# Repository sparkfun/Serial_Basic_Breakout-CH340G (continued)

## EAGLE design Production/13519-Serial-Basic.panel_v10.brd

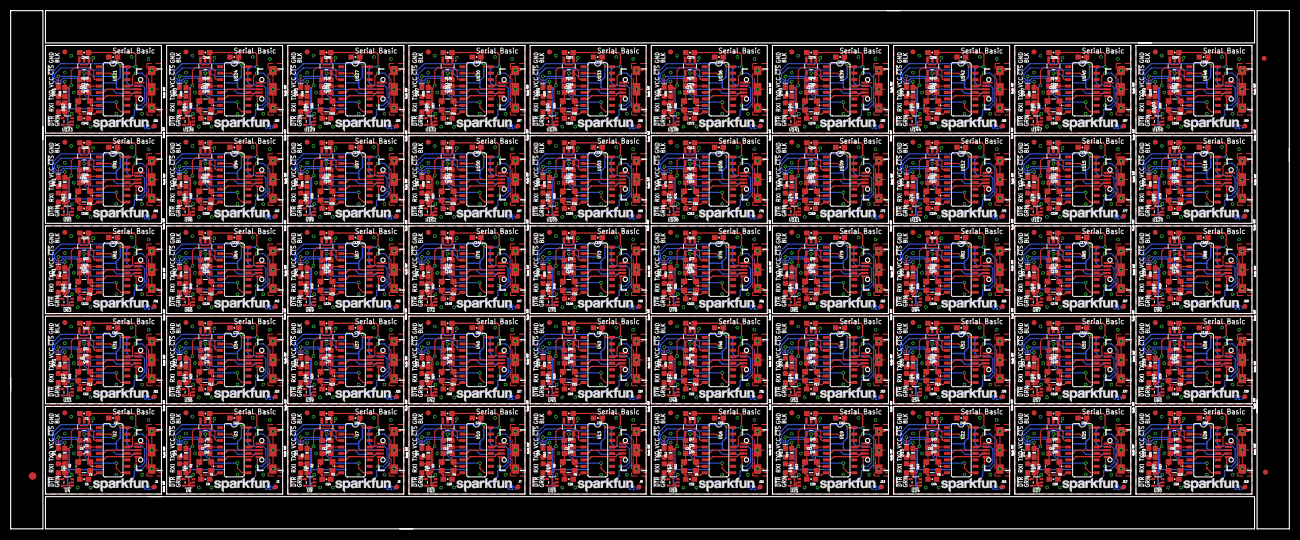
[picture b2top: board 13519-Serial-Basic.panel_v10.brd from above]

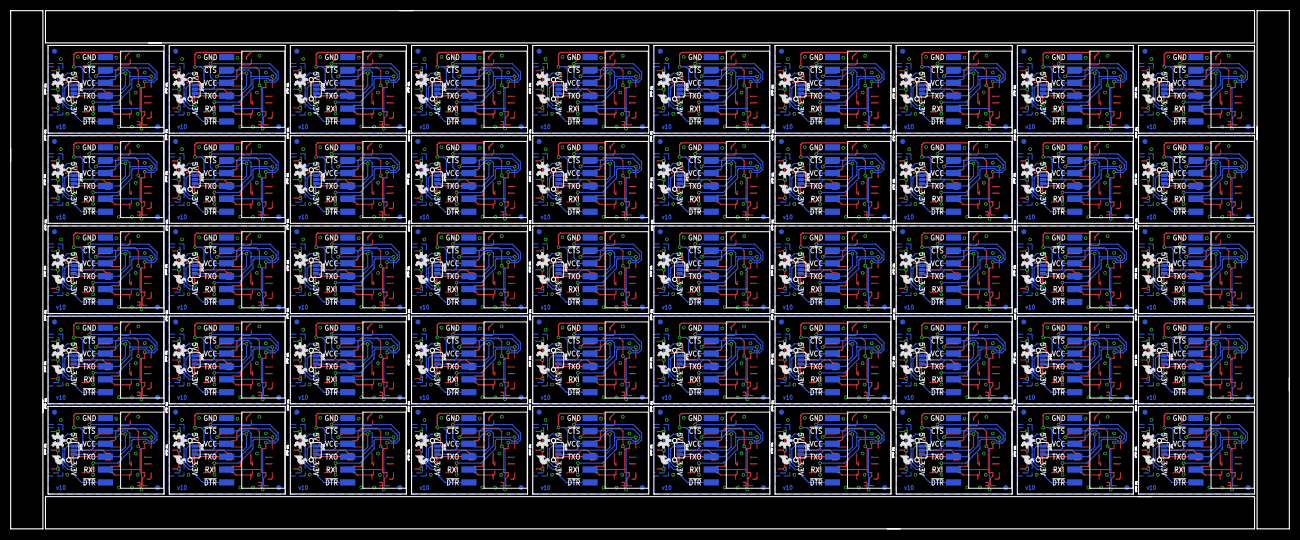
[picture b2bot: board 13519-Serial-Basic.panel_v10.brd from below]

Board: 2 copper layers, 252.0 x 102.1 mm, 1203 parts (300 on the bottom side), 850 nets.

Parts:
C1, C2, C9, C10, C15, C16, C21, C22, C27, C28, C33, C34, C39, C40, C45, C46, C51, C52, C57, C58, C63, C64, C69, C70, C75, C76, C81, C82, C87, C88, C93, C94, C99, C100, C105, C106, C111, C112, C117, C118, C123, C124, C129, C130, C135, C136, C141, C142, C147, C148, C153, C154, C159, C160, C165, C166, C171, C172, C177, C178, C183, C184, C189, C190, C195, C196, C201, C202, C207, C208, C213, C214, C219, C220, C225, C226, C231, C232, C237, C238, C243, C244, C249, C250, C255, C256, C261, C262, C267, C268, C273, C274, C279, C280, C285, C286, C291, C292, C297, C298: 1.0uF; 0603-CAP
C3, C12, C18, C24, C30, C36, C42, C48, C54, C60, C66, C72, C78, C84, C90, C96, C102, C108, C114, C120, C126, C132, C138, C144, C150, C156, C162, C168, C174, C180, C186, C192, C198, C204, C210, C216, C222, C228, C234, C240, C246, C252, C258, C264, C270, C276, C282, C288, C294, C300: 0.1uF; 0603-CAP
C4, C5, C7, C8, C13, C14, C19, C20, C25, C26, C31, C32, C37, C38, C43, C44, C49, C50, C55, C56, C61, C62, C67, C68, C73, C74, C79, C80, C85, C86, C91, C92, C97, C98, C103, C104, C109, C110, C115, C116, C121, C122, C127, C128, C133, C134, C139, C140, C145, C146, C151, C152, C157, C158, C163, C164, C169, C170, C175, C176, C181, C182, C187, C188, C193, C194, C199, C200, C205, C206, C211, C212, C217, C218, C223, C224, C229, C230, C235, C236, C241, C242, C247, C248, C253, C254, C259, C260, C265, C266, C271, C272, C277, C278, C283, C284, C289, C290, C295, C296: 10pF; 0603-CAP
C6, C11, C17, C23, C29, C35, C41, C47, C53, C59, C65, C71, C77, C83, C89, C95, C101, C107, C113, C119, C125, C131, C137, C143, C149, C155, C161, C167, C173, C179, C185, C191, C197, C203, C209, C215, C221, C227, C233, C239, C245, C251, C257, C263, C269, C275, C281, C287, C293, C299: 10nF; 0603-CAP
D1, D3, D5, D7, D9, D11, D13, D15, D17, D19, D21, D23, D25, D27, D29, D31, D33, D35, D37, D39, D41, D43, D45, D47, D49, D51, D53, D55, D57, D59, D61, D63, D65, D67, D69, D71, D73, D75, D77, D79, D81, D83, D85, D87, D89, D91, D93, D95, D97, D99: GREEN; LED-0603
D2, D4, D6, D8, D10, D12, D14, D16, D18, D20, D22, D24, D26, D28, D30, D32, D34, D36, D38, D40, D42, D44, D46, D48, D50, D52, D54, D56, D58, D60, D62, D64, D66, D68, D70, D72, D74, D76, D78, D80, D82, D84, D86, D88, D90, D92, D94, D96, D98, D100: Yellow; LED-0603
E$1: FIDUCIAL-1.5X3
E$5, E$6: FIDUCIAL-1X2
J1, J3, J5, J7, J9, J11, J13, J15, J17, J19, J21, J23, J25, J27, J29, J31, J33, J35, J37, J39, J41, J43, J45, J47, J49, J51, J53, J55, J57, J59, J61, J63, J65, J67, J69, J71, J73, J75, J77, J79, J81, J83, J85, J87, J89, J91, J93, J95, J97, J99: microB; USB-B-MICRO-SMD_V03
J2, J4, J6, J8, J10, J12, J14, J16, J18, J20, J22, J24, J26, J28, J30, J32, J34, J36, J38, J40, J42, J44, J46, J48, J50, J52, J54, J56, J58, J60, J62, J64, J66, J68, J70, J72, J74, J76, J78, J80, J82, J84, J86, J88, J90, J92, J94, J96, J98, J100: 1X06-SMD-FEMALE-V2
JP1, JP10, JP15, JP20, JP25, JP30, JP35, JP40, JP45, JP50, JP55, JP60, JP65, JP70, JP75, JP80, JP85, JP90, JP95, JP100, JP105, JP110, JP115, JP120, JP125, JP130, JP135, JP140, JP145, JP150, JP155, JP160, JP165, JP170, JP175, JP180, JP185, JP190, JP195, JP200, JP205, JP210, JP215, JP220, JP225, JP230, JP235, JP240, JP245, JP250: PAD-JUMPER-3-2OF3_NC_BY_PASTE_YES_SILK_FULL_BOX
JP2, JP3, JP4, JP5, JP6, JP7, JP8, JP9, JP11, JP12, JP13, JP14, JP16, JP17, JP18, JP19, JP21, JP22, JP23, JP24, JP26, JP27, JP28, JP29, JP31, JP32, JP33, JP34, JP36, JP37, JP38, JP39, JP41, JP42, JP43, JP44, JP46, JP47, JP48, JP49, JP51, JP52, JP53, JP54, JP56, JP57, JP58, JP59, JP61, JP62, JP63, JP64, JP66, JP67, JP68, JP69, JP71, JP72, JP73, JP74, JP76, JP77, JP78, JP79, JP81, JP82, JP83, JP84, JP86, JP87, JP88, JP89, JP91, JP92, JP93, JP94, JP96, JP97, JP98, JP99, JP101, JP102, JP103, JP104, JP106, JP107, JP108, JP109, JP111, JP112, JP113, JP114, JP116, JP117, JP118, JP119, JP121, JP122, JP123, JP124, JP126, JP127, JP128, JP129, JP131, JP132, JP133, JP134, JP136, JP137, JP138, JP139, JP141, JP142, JP143, JP144, JP146, JP147, JP148, JP149, JP151, JP152, JP153, JP154, JP156, JP157, JP158, JP159, JP161, JP162, JP163, JP164, JP166, JP167, JP168, JP169, JP171, JP172, JP173, JP174, JP176, JP177, JP178, JP179, JP181, JP182, JP183, JP184, JP186, JP187, JP188, JP189, JP191, JP192, JP193, JP194, JP196, JP197, JP198, JP199, JP201, JP202, JP203, JP204, JP206, JP207, JP208, JP209, JP211, JP212, JP213, JP214, JP216, JP217, JP218, JP219, JP221, JP222, JP223, JP224, JP226, JP227, JP228, JP229, JP231, JP232, JP233, JP234, JP236, JP237, JP238, JP239, JP241, JP242, JP243, JP244, JP246, JP247, JP248, JP249: FIDUCIAL1X2; FIDUCIAL-1X2
LOGO1, LOGO4, LOGO7, LOGO10, LOGO13, LOGO16, LOGO19, LOGO22, LOGO25, LOGO28, LOGO31, LOGO34, LOGO37, LOGO40, LOGO43, LOGO46, LOGO49, LOGO52, LOGO55, LOGO58, LOGO61, LOGO64, LOGO67, LOGO70, LOGO73, LOGO76, LOGO79, LOGO82, LOGO85, LOGO88, LOGO91, LOGO94, LOGO97, LOGO100, LOGO103, LOGO106, LOGO109, LOGO112, LOGO115, LOGO118, LOGO121, LOGO124, LOGO127, LOGO130, LOGO133, LOGO136, LOGO139, LOGO142, LOGO145, LOGO148: OSHW-LOGOS; OSHW-LOGO-S
LOGO2, LOGO6, LOGO9, LOGO12, LOGO15, LOGO18, LOGO21, LOGO24, LOGO27, LOGO30, LOGO33, LOGO36, LOGO39, LOGO42, LOGO45, LOGO48, LOGO51, LOGO54, LOGO57, LOGO60, LOGO63, LOGO66, LOGO69, LOGO72, LOGO75, LOGO78, LOGO81, LOGO84, LOGO87, LOGO90, LOGO93, LOGO96, LOGO99, LOGO102, LOGO105, LOGO108, LOGO111, LOGO114, LOGO117, LOGO120, LOGO123, LOGO126, LOGO129, LOGO132, LOGO135, LOGO138, LOGO141, LOGO144, LOGO147, LOGO150: SFE_LOGO_FLAME.1_INCH; SFE_LOGO_FLAME_.1
LOGO3, LOGO5, LOGO8, LOGO11, LOGO14, LOGO17, LOGO20, LOGO23, LOGO26, LOGO29, LOGO32, LOGO35, LOGO38, LOGO41, LOGO44, LOGO47, LOGO50, LOGO53, LOGO56, LOGO59, LOGO62, LOGO65, LOGO68, LOGO71, LOGO74, LOGO77, LOGO80, LOGO83, LOGO86, LOGO89, LOGO92, LOGO95, LOGO98, LOGO101, LOGO104, LOGO107, LOGO110, LOGO113, LOGO116, LOGO119, LOGO122, LOGO125, LOGO128, LOGO131, LOGO134, LOGO137, LOGO140, LOGO143, LOGO146, LOGO149: SFE_LOGO_NAME.1_INCH; SFE_LOGO_NAME_.1
R1, R2, R5, R7, R9, R11, R13, R15, R17, R19, R21, R23, R25, R27, R29, R31, R33, R35, R37, R39, R41, R43, R45, R47, R49, R51, R53, R55, R57, R59, R61, R63, R65, R67, R69, R71, R73, R75, R77, R79, R81, R83, R85, R87, R89, R91, R93, R95, R97, R99: 1K; 0603-RES
R3, R4, R6, R8, R10, R12, R14, R16, R18, R20, R22, R24, R26, R28, R30, R32, R34, R36, R38, R40, R42, R44, R46, R48, R50, R52, R54, R56, R58, R60, R62, R64, R66, R68, R70, R72, R74, R76, R78, R80, R82, R84, R86, R88, R90, R92, R94, R96, R98, R100: 330; 0603-RES
U1, U5, U8, U11, U14, U17, U20, U23, U26, U29, U32, U35, U38, U41, U44, U47, U50, U53, U56, U59, U62, U65, U68, U71, U74, U77, U80, U83, U86, U89, U92, U95, U98, U101, U104, U107, U110, U113, U116, U119, U122, U125, U128, U131, U134, U137, U140, U143, U146, U149: AP2112-3.3V; SOT23-5
U2, U3, U7, U10, U13, U16, U19, U22, U25, U28, U31, U34, U37, U40, U43, U46, U49, U52, U55, U58, U61, U64, U67, U70, U73, U76, U79, U82, U85, U88, U91, U94, U97, U100, U103, U106, U109, U112, U115, U118, U121, U124, U127, U130, U133, U136, U139, U142, U145, U148: CH340G; SO016
U4, U6, U9, U12, U15, U18, U21, U24, U27, U30, U33, U36, U39, U42, U45, U48, U51, U54, U57, U60, U63, U66, U69, U72, U75, U78, U81, U84, U87, U90, U93, U96, U99, U102, U105, U108, U111, U114, U117, U120, U123, U126, U129, U132, U135, U138, U141, U144, U147, U150: 74LVC1G08SE; SOT353
Y1, Y2, Y3, Y4, Y5, Y6, Y7, Y8, Y9, Y10, Y11, Y12, Y13, Y14, Y15, Y16, Y17, Y18, Y19, Y20, Y21, Y22, Y23, Y24, Y25, Y26, Y27, Y28, Y29, Y30, Y31, Y32, Y33, Y34, Y35, Y36, Y37, Y38, Y39, Y40, Y41, Y42, Y43, Y44, Y45, Y46, Y47, Y48, Y49, Y50: 12MHz; CRYSTAL-SMD-3.2X2.5

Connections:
3.3V: C2.1, JP1.3, U1.5
3.3V1: C10.1, JP10.3, U5.5
3.3V2: C16.1, JP15.3, U8.5
3.3V3: C22.1, JP20.3, U11.5
3.3V4: C28.1, JP25.3, U14.5
3.3V5: C34.1, JP30.3, U17.5
3.3V6: C40.1, JP35.3, U20.5
3.3V7: C46.1, JP40.3, U23.5
3.3V8: C52.1, JP45.3, U26.5
3.3V9: C58.1, JP50.3, U29.5
3.3V10: C64.1, JP55.3, U32.5
3.3V11: C70.1, JP60.3, U35.5
3.3V12: C76.1, JP65.3, U38.5
3.3V13: C82.1, JP70.3, U41.5
3.3V14: C88.1, JP75.3, U44.5
3.3V15: C94.1, JP80.3, U47.5
3.3V16: C100.1, JP85.3, U50.5
3.3V17: C106.1, JP90.3, U53.5
3.3V18: C112.1, JP95.3, U56.5
3.3V19: C118.1, JP100.3, U59.5
3.3V20: C124.1, JP105.3, U62.5
3.3V21: C130.1, JP110.3, U65.5
3.3V22: C136.1, JP115.3, U68.5
3.3V23: C142.1, JP120.3, U71.5
3.3V24: C148.1, JP125.3, U74.5
3.3V25: C154.1, JP130.3, U77.5
3.3V26: C160.1, JP135.3, U80.5
3.3V27: C166.1, JP140.3, U83.5
3.3V28: C172.1, JP145.3, U86.5
3.3V29: C178.1, JP150.3, U89.5
3.3V30: C184.1, JP155.3, U92.5
3.3V31: C190.1, JP160.3, U95.5
3.3V32: C196.1, JP165.3, U98.5
3.3V33: C202.1, JP170.3, U101.5
3.3V34: C208.1, JP175.3, U104.5
3.3V35: C214.1, JP180.3, U107.5
3.3V36: C220.1, JP185.3, U110.5
3.3V37: C226.1, JP190.3, U113.5
3.3V38: C232.1, JP195.3, U116.5
3.3V39: C238.1, JP200.3, U119.5
3.3V40: C244.1, JP205.3, U122.5
3.3V41: C250.1, JP210.3, U125.5
3.3V42: C256.1, JP215.3, U128.5
3.3V43: C262.1, JP220.3, U131.5
3.3V44: C268.1, JP225.3, U134.5
3.3V45: C274.1, JP230.3, U137.5
3.3V46: C280.1, JP235.3, U140.5
3.3V47: C286.1, JP240.3, U143.5
3.3V48: C292.1, JP245.3, U146.5
3.3V49: C298.1, JP250.3, U149.5
5V: C1.1, J1.VBUS, JP1.1, U1.1, U1.3
5V1: C9.1, J3.VBUS, JP10.1, U5.1, U5.3
5V2: C15.1, J5.VBUS, JP15.1, U8.1, U8.3
5V3: C21.1, J7.VBUS, JP20.1, U11.1, U11.3
5V4: C27.1, J9.VBUS, JP25.1, U14.1, U14.3
5V5: C33.1, J11.VBUS, JP30.1, U17.1, U17.3
5V6: C39.1, J13.VBUS, JP35.1, U20.1, U20.3
5V7: C45.1, J15.VBUS, JP40.1, U23.1, U23.3
5V8: C51.1, J17.VBUS, JP45.1, U26.1, U26.3
5V9: C57.1, J19.VBUS, JP50.1, U29.1, U29.3
5V10: C63.1, J21.VBUS, JP55.1, U32.1, U32.3
5V11: C69.1, J23.VBUS, JP60.1, U35.1, U35.3
5V12: C75.1, J25.VBUS, JP65.1, U38.1, U38.3
5V13: C81.1, J27.VBUS, JP70.1, U41.1, U41.3
5V14: C87.1, J29.VBUS, JP75.1, U44.1, U44.3
5V15: C93.1, J31.VBUS, JP80.1, U47.1, U47.3
5V16: C99.1, J33.VBUS, JP85.1, U50.1, U50.3
5V17: C105.1, J35.VBUS, JP90.1, U53.1, U53.3
5V18: C111.1, J37.VBUS, JP95.1, U56.1, U56.3
5V19: C117.1, J39.VBUS, JP100.1, U59.1, U59.3
5V20: C123.1, J41.VBUS, JP105.1, U62.1, U62.3
5V21: C129.1, J43.VBUS, JP110.1, U65.1, U65.3
5V22: C135.1, J45.VBUS, JP115.1, U68.1, U68.3
5V23: C141.1, J47.VBUS, JP120.1, U71.1, U71.3
5V24: C147.1, J49.VBUS, JP125.1, U74.1, U74.3
5V25: C153.1, J51.VBUS, JP130.1, U77.1, U77.3
5V26: C159.1, J53.VBUS, JP135.1, U80.1, U80.3
5V27: C165.1, J55.VBUS, JP140.1, U83.1, U83.3
5V28: C171.1, J57.VBUS, JP145.1, U86.1, U86.3
5V29: C177.1, J59.VBUS, JP150.1, U89.1, U89.3
5V30: C183.1, J61.VBUS, JP155.1, U92.1, U92.3
5V31: C189.1, J63.VBUS, JP160.1, U95.1, U95.3
5V32: C195.1, J65.VBUS, JP165.1, U98.1, U98.3
5V33: C201.1, J67.VBUS, JP170.1, U101.1, U101.3
5V34: C207.1, J69.VBUS, JP175.1, U104.1, U104.3
5V35: C213.1, J71.VBUS, JP180.1, U107.1, U107.3
5V36: C219.1, J73.VBUS, JP185.1, U110.1, U110.3
5V37: C225.1, J75.VBUS, JP190.1, U113.1, U113.3
5V38: C231.1, J77.VBUS, JP195.1, U116.1, U116.3
5V39: C237.1, J79.VBUS, JP200.1, U119.1, U119.3
5V40: C243.1, J81.VBUS, JP205.1, U122.1, U122.3
5V41: C249.1, J83.VBUS, JP210.1, U125.1, U125.3
5V42: C255.1, J85.VBUS, JP215.1, U128.1, U128.3
5V43: C261.1, J87.VBUS, JP220.1, U131.1, U131.3
5V44: C267.1, J89.VBUS, JP225.1, U134.1, U134.3
5V45: C273.1, J91.VBUS, JP230.1, U137.1, U137.3
5V46: C279.1, J93.VBUS, JP235.1, U140.1, U140.3
5V47: C285.1, J95.VBUS, JP240.1, U143.1, U143.3
5V48: C291.1, J97.VBUS, JP245.1, U146.1, U146.3
5V49: C297.1, J99.VBUS, JP250.1, U149.1, U149.3
!CTS: J2.2, U2.9
!CTS1: J4.2, U3.9
!CTS2: J6.2, U7.9
!CTS3: J8.2, U10.9
!CTS4: J10.2, U13.9
!CTS5: J12.2, U16.9
!CTS6: J14.2, U19.9
!CTS7: J16.2, U22.9
!CTS8: J18.2, U25.9
!CTS9: J20.2, U28.9
!CTS10: J22.2, U31.9
!CTS11: J24.2, U34.9
!CTS12: J26.2, U37.9
!CTS13: J28.2, U40.9
!CTS14: J30.2, U43.9
!CTS15: J32.2, U46.9
!CTS16: J34.2, U49.9
!CTS17: J36.2, U52.9
!CTS18: J38.2, U55.9
!CTS19: J40.2, U58.9
!CTS20: J42.2, U61.9
!CTS21: J44.2, U64.9
!CTS22: J46.2, U67.9
!CTS23: J48.2, U70.9
!CTS24: J50.2, U73.9
!CTS25: J52.2, U76.9
!CTS26: J54.2, U79.9
!CTS27: J56.2, U82.9
!CTS28: J58.2, U85.9
!CTS29: J60.2, U88.9
!CTS30: J62.2, U91.9
!CTS31: J64.2, U94.9
!CTS32: J66.2, U97.9
!CTS33: J68.2, U100.9
!CTS34: J70.2, U103.9
!CTS35: J72.2, U106.9
!CTS36: J74.2, U109.9
!CTS37: J76.2, U112.9
!CTS38: J78.2, U115.9
!CTS39: J80.2, U118.9
!CTS40: J82.2, U121.9
!CTS41: J84.2, U124.9
!CTS42: J86.2, U127.9
!CTS43: J88.2, U130.9
!CTS44: J90.2, U133.9
!CTS45: J92.2, U136.9
!CTS46: J94.2, U139.9
!CTS47: J96.2, U142.9
!CTS48: J98.2, U145.9
!CTS49: J100.2, U148.9
!DTR: J2.6, U2.13
!DTR1: J4.6, U3.13
!DTR2: J6.6, U7.13
!DTR3: J8.6, U10.13
!DTR4: J10.6, U13.13
!DTR5: J12.6, U16.13
!DTR6: J14.6, U19.13
!DTR7: J16.6, U22.13
!DTR8: J18.6, U25.13
!DTR9: J20.6, U28.13
!DTR10: J22.6, U31.13
!DTR11: J24.6, U34.13
!DTR12: J26.6, U37.13
!DTR13: J28.6, U40.13
!DTR14: J30.6, U43.13
!DTR15: J32.6, U46.13
!DTR16: J34.6, U49.13
!DTR17: J36.6, U52.13
!DTR18: J38.6, U55.13
!DTR19: J40.6, U58.13
!DTR20: J42.6, U61.13
!DTR21: J44.6, U64.13
!DTR22: J46.6, U67.13
!DTR23: J48.6, U70.13
!DTR24: J50.6, U73.13
!DTR25: J52.6, U76.13
!DTR26: J54.6, U79.13
!DTR27: J56.6, U82.13
!DTR28: J58.6, U85.13
!DTR29: J60.6, U88.13
!DTR30: J62.6, U91.13
!DTR31: J64.6, U94.13
!DTR32: J66.6, U97.13
!DTR33: J68.6, U100.13
!DTR34: J70.6, U103.13
!DTR35: J72.6, U106.13
!DTR36: J74.6, U109.13
!DTR37: J76.6, U112.13
!DTR38: J78.6, U115.13
!DTR39: J80.6, U118.13
!DTR40: J82.6, U121.13
!DTR41: J84.6, U124.13
!DTR42: J86.6, U127.13
!DTR43: J88.6, U130.13
!DTR44: J90.6, U133.13
!DTR45: J92.6, U136.13
!DTR46: J94.6, U139.13
!DTR47: J96.6, U142.13
!DTR48: J98.6, U145.13
!DTR49: J100.6, U148.13
GND: C1.2, C2.2, C3.2, C4.1, C5.1, C6.2, J1.GND, J2.1, U1.2, U2.1, U4.3, Y2.2, Y2.4
GND1: C7.1, C8.1, C9.2, C10.2, C11.2, C12.2, J3.GND, J4.1, U3.1, U5.2, U6.3, Y1.2, Y1.4
GND2: C13.1, C14.1, C15.2, C16.2, C17.2, C18.2, J5.GND, J6.1, U7.1, U8.2, U9.3, Y3.2, Y3.4
GND3: C19.1, C20.1, C21.2, C22.2, C23.2, C24.2, J7.GND, J8.1, U10.1, U11.2, U12.3, Y4.2, Y4.4
GND4: C25.1, C26.1, C27.2, C28.2, C29.2, C30.2, J9.GND, J10.1, U13.1, U14.2, U15.3, Y5.2, Y5.4
GND5: C31.1, C32.1, C33.2, C34.2, C35.2, C36.2, J11.GND, J12.1, U16.1, U17.2, U18.3, Y6.2, Y6.4
GND6: C37.1, C38.1, C39.2, C40.2, C41.2, C42.2, J13.GND, J14.1, U19.1, U20.2, U21.3, Y7.2, Y7.4
GND7: C43.1, C44.1, C45.2, C46.2, C47.2, C48.2, J15.GND, J16.1, U22.1, U23.2, U24.3, Y8.2, Y8.4
GND8: C49.1, C50.1, C51.2, C52.2, C53.2, C54.2, J17.GND, J18.1, U25.1, U26.2, U27.3, Y9.2, Y9.4
GND9: C55.1, C56.1, C57.2, C58.2, C59.2, C60.2, J19.GND, J20.1, U28.1, U29.2, U30.3, Y10.2, Y10.4
GND10: C61.1, C62.1, C63.2, C64.2, C65.2, C66.2, J21.GND, J22.1, U31.1, U32.2, U33.3, Y11.2, Y11.4
GND11: C67.1, C68.1, C69.2, C70.2, C71.2, C72.2, J23.GND, J24.1, U34.1, U35.2, U36.3, Y12.2, Y12.4
GND12: C73.1, C74.1, C75.2, C76.2, C77.2, C78.2, J25.GND, J26.1, U37.1, U38.2, U39.3, Y13.2, Y13.4
GND13: C79.1, C80.1, C81.2, C82.2, C83.2, C84.2, J27.GND, J28.1, U40.1, U41.2, U42.3, Y14.2, Y14.4
GND14: C85.1, C86.1, C87.2, C88.2, C89.2, C90.2, J29.GND, J30.1, U43.1, U44.2, U45.3, Y15.2, Y15.4
GND15: C91.1, C92.1, C93.2, C94.2, C95.2, C96.2, J31.GND, J32.1, U46.1, U47.2, U48.3, Y16.2, Y16.4
GND16: C97.1, C98.1, C99.2, C100.2, C101.2, C102.2, J33.GND, J34.1, U49.1, U50.2, U51.3, Y17.2, Y17.4
GND17: C103.1, C104.1, C105.2, C106.2, C107.2, C108.2, J35.GND, J36.1, U52.1, U53.2, U54.3, Y18.2, Y18.4
GND18: C109.1, C110.1, C111.2, C112.2, C113.2, C114.2, J37.GND, J38.1, U55.1, U56.2, U57.3, Y19.2, Y19.4
GND19: C115.1, C116.1, C117.2, C118.2, C119.2, C120.2, J39.GND, J40.1, U58.1, U59.2, U60.3, Y20.2, Y20.4
GND20: C121.1, C122.1, C123.2, C124.2, C125.2, C126.2, J41.GND, J42.1, U61.1, U62.2, U63.3, Y21.2, Y21.4
GND21: C127.1, C128.1, C129.2, C130.2, C131.2, C132.2, J43.GND, J44.1, U64.1, U65.2, U66.3, Y22.2, Y22.4
GND22: C133.1, C134.1, C135.2, C136.2, C137.2, C138.2, J45.GND, J46.1, U67.1, U68.2, U69.3, Y23.2, Y23.4
GND23: C139.1, C140.1, C141.2, C142.2, C143.2, C144.2, J47.GND, J48.1, U70.1, U71.2, U72.3, Y24.2, Y24.4
GND24: C145.1, C146.1, C147.2, C148.2, C149.2, C150.2, J49.GND, J50.1, U73.1, U74.2, U75.3, Y25.2, Y25.4
GND25: C151.1, C152.1, C153.2, C154.2, C155.2, C156.2, J51.GND, J52.1, U76.1, U77.2, U78.3, Y26.2, Y26.4
GND26: C157.1, C158.1, C159.2, C160.2, C161.2, C162.2, J53.GND, J54.1, U79.1, U80.2, U81.3, Y27.2, Y27.4
GND27: C163.1, C164.1, C165.2, C166.2, C167.2, C168.2, J55.GND, J56.1, U82.1, U83.2, U84.3, Y28.2, Y28.4
GND28: C169.1, C170.1, C171.2, C172.2, C173.2, C174.2, J57.GND, J58.1, U85.1, U86.2, U87.3, Y29.2, Y29.4
GND29: C175.1, C176.1, C177.2, C178.2, C179.2, C180.2, J59.GND, J60.1, U88.1, U89.2, U90.3, Y30.2, Y30.4
GND30: C181.1, C182.1, C183.2, C184.2, C185.2, C186.2, J61.GND, J62.1, U91.1, U92.2, U93.3, Y31.2, Y31.4
GND31: C187.1, C188.1, C189.2, C190.2, C191.2, C192.2, J63.GND, J64.1, U94.1, U95.2, U96.3, Y32.2, Y32.4
GND32: C193.1, C194.1, C195.2, C196.2, C197.2, C198.2, J65.GND, J66.1, U97.1, U98.2, U99.3, Y33.2, Y33.4
GND33: C199.1, C200.1, C201.2, C202.2, C203.2, C204.2, J67.GND, J68.1, U100.1, U101.2, U102.3, Y34.2, Y34.4
GND34: C205.1, C206.1, C207.2, C208.2, C209.2, C210.2, J69.GND, J70.1, U103.1, U104.2, U105.3, Y35.2, Y35.4
GND35: C211.1, C212.1, C213.2, C214.2, C215.2, C216.2, J71.GND, J72.1, U106.1, U107.2, U108.3, Y36.2, Y36.4
GND36: C217.1, C218.1, C219.2, C220.2, C221.2, C222.2, J73.GND, J74.1, U109.1, U110.2, U111.3, Y37.2, Y37.4
GND37: C223.1, C224.1, C225.2, C226.2, C227.2, C228.2, J75.GND, J76.1, U112.1, U113.2, U114.3, Y38.2, Y38.4
GND38: C229.1, C230.1, C231.2, C232.2, C233.2, C234.2, J77.GND, J78.1, U115.1, U116.2, U117.3, Y39.2, Y39.4
GND39: C235.1, C236.1, C237.2, C238.2, C239.2, C240.2, J79.GND, J80.1, U118.1, U119.2, U120.3, Y40.2, Y40.4
GND40: C241.1, C242.1, C243.2, C244.2, C245.2, C246.2, J81.GND, J82.1, U121.1, U122.2, U123.3, Y41.2, Y41.4
GND41: C247.1, C248.1, C249.2, C250.2, C251.2, C252.2, J83.GND, J84.1, U124.1, U125.2, U126.3, Y42.2, Y42.4
GND42: C253.1, C254.1, C255.2, C256.2, C257.2, C258.2, J85.GND, J86.1, U127.1, U128.2, U129.3, Y43.2, Y43.4
GND43: C259.1, C260.1, C261.2, C262.2, C263.2, C264.2, J87.GND, J88.1, U130.1, U131.2, U132.3, Y44.2, Y44.4
GND44: C265.1, C266.1, C267.2, C268.2, C269.2, C270.2, J89.GND, J90.1, U133.1, U134.2, U135.3, Y45.2, Y45.4
GND45: C271.1, C272.1, C273.2, C274.2, C275.2, C276.2, J91.GND, J92.1, U136.1, U137.2, U138.3, Y46.2, Y46.4
GND46: C277.1, C278.1, C279.2, C280.2, C281.2, C282.2, J93.GND, J94.1, U139.1, U140.2, U141.3, Y47.2, Y47.4
GND47: C283.1, C284.1, C285.2, C286.2, C287.2, C288.2, J95.GND, J96.1, U142.1, U143.2, U144.3, Y48.2, Y48.4
GND48: C289.1, C290.1, C291.2, C292.2, C293.2, C294.2, J97.GND, J98.1, U145.1, U146.2, U147.3, Y49.2, Y49.4
GND49: C295.1, C296.1, C297.2, C298.2, C299.2, C300.2, J99.GND, J100.1, U148.1, U149.2, U150.3, Y50.2, Y50.4
unnamed: D1.A, R3.1
unnamed: D2.A, R2.1
unnamed: C5.2, U2.8, Y2.3
unnamed: C4.2, U2.7, Y2.1
unnamed: D2.C, U4.4
unnamed: J1.D-, U2.6
unnamed: J1.D+, U2.5
unnamed: D3.A, R4.1
unnamed: D4.A, R1.1
unnamed: C8.2, U3.8, Y1.3
unnamed: C7.2, U3.7, Y1.1
unnamed: J3.D-, U3.6
unnamed: J3.D+, U3.5
unnamed: D4.C, U6.4
unnamed: D5.A, R6.1
unnamed: D6.A, R5.1
unnamed: C14.2, U7.8, Y3.3
unnamed: C13.2, U7.7, Y3.1
unnamed: J5.D-, U7.6
unnamed: J5.D+, U7.5
unnamed: D6.C, U9.4
unnamed: D7.A, R8.1
unnamed: D8.A, R7.1
unnamed: C20.2, U10.8, Y4.3
unnamed: C19.2, U10.7, Y4.1
unnamed: J7.D-, U10.6
unnamed: J7.D+, U10.5
unnamed: D8.C, U12.4
unnamed: D9.A, R10.1
unnamed: D10.A, R9.1
unnamed: C26.2, U13.8, Y5.3
unnamed: C25.2, U13.7, Y5.1
unnamed: J9.D-, U13.6
unnamed: J9.D+, U13.5
unnamed: D10.C, U15.4
unnamed: D11.A, R12.1
unnamed: D12.A, R11.1
unnamed: C32.2, U16.8, Y6.3
unnamed: C31.2, U16.7, Y6.1
unnamed: J11.D-, U16.6
unnamed: J11.D+, U16.5
unnamed: D12.C, U18.4
unnamed: D13.A, R14.1
unnamed: D14.A, R13.1
unnamed: C38.2, U19.8, Y7.3
unnamed: C37.2, U19.7, Y7.1
unnamed: J13.D-, U19.6
unnamed: J13.D+, U19.5
unnamed: D14.C, U21.4
unnamed: D15.A, R16.1
unnamed: D16.A, R15.1
unnamed: C44.2, U22.8, Y8.3
unnamed: C43.2, U22.7, Y8.1
unnamed: J15.D-, U22.6
unnamed: J15.D+, U22.5
unnamed: D16.C, U24.4
unnamed: D17.A, R18.1
unnamed: D18.A, R17.1
unnamed: C50.2, U25.8, Y9.3
unnamed: C49.2, U25.7, Y9.1
unnamed: J17.D-, U25.6
unnamed: J17.D+, U25.5
unnamed: D18.C, U27.4
unnamed: D19.A, R20.1
unnamed: D20.A, R19.1
unnamed: C56.2, U28.8, Y10.3
unnamed: C55.2, U28.7, Y10.1
unnamed: J19.D-, U28.6
unnamed: J19.D+, U28.5
unnamed: D20.C, U30.4
unnamed: D21.A, R22.1
unnamed: D22.A, R21.1
unnamed: C62.2, U31.8, Y11.3
unnamed: C61.2, U31.7, Y11.1
unnamed: J21.D-, U31.6
unnamed: J21.D+, U31.5
unnamed: D22.C, U33.4
unnamed: D23.A, R24.1
unnamed: D24.A, R23.1
unnamed: C68.2, U34.8, Y12.3
unnamed: C67.2, U34.7, Y12.1
unnamed: J23.D-, U34.6
unnamed: J23.D+, U34.5
unnamed: D24.C, U36.4
unnamed: D25.A, R26.1
unnamed: D26.A, R25.1
unnamed: C74.2, U37.8, Y13.3
unnamed: C73.2, U37.7, Y13.1
unnamed: J25.D-, U37.6
unnamed: J25.D+, U37.5
unnamed: D26.C, U39.4
unnamed: D27.A, R28.1
unnamed: D28.A, R27.1
unnamed: C80.2, U40.8, Y14.3
unnamed: C79.2, U40.7, Y14.1
unnamed: J27.D-, U40.6
unnamed: J27.D+, U40.5
unnamed: D28.C, U42.4
unnamed: D29.A, R30.1
unnamed: D30.A, R29.1
unnamed: C86.2, U43.8, Y15.3
unnamed: C85.2, U43.7, Y15.1
unnamed: J29.D-, U43.6
unnamed: J29.D+, U43.5
unnamed: D30.C, U45.4
unnamed: D31.A, R32.1
unnamed: D32.A, R31.1
unnamed: C92.2, U46.8, Y16.3
unnamed: C91.2, U46.7, Y16.1
unnamed: J31.D-, U46.6
unnamed: J31.D+, U46.5
unnamed: D32.C, U48.4
unnamed: D33.A, R34.1
unnamed: D34.A, R33.1
unnamed: C98.2, U49.8, Y17.3
unnamed: C97.2, U49.7, Y17.1
unnamed: J33.D-, U49.6
unnamed: J33.D+, U49.5
unnamed: D34.C, U51.4
unnamed: D35.A, R36.1
unnamed: D36.A, R35.1
unnamed: C104.2, U52.8, Y18.3
unnamed: C103.2, U52.7, Y18.1
unnamed: J35.D-, U52.6
unnamed: J35.D+, U52.5
unnamed: D36.C, U54.4
unnamed: D37.A, R38.1
unnamed: D38.A, R37.1
unnamed: C110.2, U55.8, Y19.3
unnamed: C109.2, U55.7, Y19.1
unnamed: J37.D-, U55.6
unnamed: J37.D+, U55.5
unnamed: D38.C, U57.4
unnamed: D39.A, R40.1
unnamed: D40.A, R39.1
unnamed: C116.2, U58.8, Y20.3
unnamed: C115.2, U58.7, Y20.1
unnamed: J39.D-, U58.6
unnamed: J39.D+, U58.5
unnamed: D40.C, U60.4
unnamed: D41.A, R42.1
unnamed: D42.A, R41.1
unnamed: C122.2, U61.8, Y21.3
unnamed: C121.2, U61.7, Y21.1
unnamed: J41.D-, U61.6
unnamed: J41.D+, U61.5
unnamed: D42.C, U63.4
unnamed: D43.A, R44.1
unnamed: D44.A, R43.1
unnamed: C128.2, U64.8, Y22.3
unnamed: C127.2, U64.7, Y22.1
unnamed: J43.D-, U64.6
unnamed: J43.D+, U64.5
unnamed: D44.C, U66.4
unnamed: D45.A, R46.1
unnamed: D46.A, R45.1
unnamed: C134.2, U67.8, Y23.3
unnamed: C133.2, U67.7, Y23.1
unnamed: J45.D-, U67.6
unnamed: J45.D+, U67.5
unnamed: D46.C, U69.4
unnamed: D47.A, R48.1
unnamed: D48.A, R47.1
unnamed: C140.2, U70.8, Y24.3
unnamed: C139.2, U70.7, Y24.1
unnamed: J47.D-, U70.6
unnamed: J47.D+, U70.5
unnamed: D48.C, U72.4
unnamed: D49.A, R50.1
unnamed: D50.A, R49.1
unnamed: C146.2, U73.8, Y25.3
unnamed: C145.2, U73.7, Y25.1
unnamed: J49.D-, U73.6
unnamed: J49.D+, U73.5
unnamed: D50.C, U75.4
unnamed: D51.A, R52.1
unnamed: D52.A, R51.1
unnamed: C152.2, U76.8, Y26.3
unnamed: C151.2, U76.7, Y26.1
unnamed: J51.D-, U76.6
unnamed: J51.D+, U76.5
unnamed: D52.C, U78.4
unnamed: D53.A, R54.1
unnamed: D54.A, R53.1
unnamed: C158.2, U79.8, Y27.3
unnamed: C157.2, U79.7, Y27.1
unnamed: J53.D-, U79.6
unnamed: J53.D+, U79.5
unnamed: D54.C, U81.4
unnamed: D55.A, R56.1
unnamed: D56.A, R55.1
unnamed: C164.2, U82.8, Y28.3
unnamed: C163.2, U82.7, Y28.1
unnamed: J55.D-, U82.6
unnamed: J55.D+, U82.5
unnamed: D56.C, U84.4
unnamed: D57.A, R58.1
unnamed: D58.A, R57.1
unnamed: C170.2, U85.8, Y29.3
unnamed: C169.2, U85.7, Y29.1
unnamed: J57.D-, U85.6
unnamed: J57.D+, U85.5
unnamed: D58.C, U87.4
unnamed: D59.A, R60.1
unnamed: D60.A, R59.1
unnamed: C176.2, U88.8, Y30.3
unnamed: C175.2, U88.7, Y30.1
unnamed: J59.D-, U88.6
unnamed: J59.D+, U88.5
unnamed: D60.C, U90.4
unnamed: D61.A, R62.1
unnamed: D62.A, R61.1
unnamed: C182.2, U91.8, Y31.3
unnamed: C181.2, U91.7, Y31.1
unnamed: J61.D-, U91.6
unnamed: J61.D+, U91.5
unnamed: D62.C, U93.4
unnamed: D63.A, R64.1
unnamed: D64.A, R63.1
unnamed: C188.2, U94.8, Y32.3
unnamed: C187.2, U94.7, Y32.1
unnamed: J63.D-, U94.6
unnamed: J63.D+, U94.5
unnamed: D64.C, U96.4
unnamed: D65.A, R66.1
unnamed: D66.A, R65.1
unnamed: C194.2, U97.8, Y33.3
unnamed: C193.2, U97.7, Y33.1
unnamed: J65.D-, U97.6
unnamed: J65.D+, U97.5
unnamed: D66.C, U99.4
unnamed: D67.A, R68.1
unnamed: D68.A, R67.1
unnamed: C200.2, U100.8, Y34.3
unnamed: C199.2, U100.7, Y34.1
unnamed: J67.D-, U100.6
unnamed: J67.D+, U100.5
unnamed: D68.C, U102.4
unnamed: D69.A, R70.1
unnamed: D70.A, R69.1
unnamed: C206.2, U103.8, Y35.3
unnamed: C205.2, U103.7, Y35.1
unnamed: J69.D-, U103.6
unnamed: J69.D+, U103.5
unnamed: D70.C, U105.4
unnamed: D71.A, R72.1
unnamed: D72.A, R71.1
unnamed: C212.2, U106.8, Y36.3
unnamed: C211.2, U106.7, Y36.1
unnamed: J71.D-, U106.6
unnamed: J71.D+, U106.5
unnamed: D72.C, U108.4
unnamed: D73.A, R74.1
unnamed: D74.A, R73.1
unnamed: C218.2, U109.8, Y37.3
unnamed: C217.2, U109.7, Y37.1
unnamed: J73.D-, U109.6
unnamed: J73.D+, U109.5
unnamed: D74.C, U111.4
unnamed: D75.A, R76.1
unnamed: D76.A, R75.1
unnamed: C224.2, U112.8, Y38.3
unnamed: C223.2, U112.7, Y38.1
unnamed: J75.D-, U112.6
unnamed: J75.D+, U112.5
unnamed: D76.C, U114.4
unnamed: D77.A, R78.1
unnamed: D78.A, R77.1
unnamed: C230.2, U115.8, Y39.3
unnamed: C229.2, U115.7, Y39.1
unnamed: J77.D-, U115.6
unnamed: J77.D+, U115.5
unnamed: D78.C, U117.4
unnamed: D79.A, R80.1
unnamed: D80.A, R79.1
unnamed: C236.2, U118.8, Y40.3
unnamed: C235.2, U118.7, Y40.1
unnamed: J79.D-, U118.6
unnamed: J79.D+, U118.5
unnamed: D80.C, U120.4
unnamed: D81.A, R82.1
unnamed: D82.A, R81.1
unnamed: C242.2, U121.8, Y41.3
unnamed: C241.2, U121.7, Y41.1
unnamed: J81.D-, U121.6
unnamed: J81.D+, U121.5
unnamed: D82.C, U123.4
unnamed: D83.A, R84.1
unnamed: D84.A, R83.1
unnamed: C248.2, U124.8, Y42.3
unnamed: C247.2, U124.7, Y42.1
unnamed: J83.D-, U124.6
unnamed: J83.D+, U124.5
unnamed: D84.C, U126.4
unnamed: D85.A, R86.1
unnamed: D86.A, R85.1
unnamed: C254.2, U127.8, Y43.3
unnamed: C253.2, U127.7, Y43.1
unnamed: J85.D-, U127.6
unnamed: J85.D+, U127.5
unnamed: D86.C, U129.4
unnamed: D87.A, R88.1
unnamed: D88.A, R87.1
unnamed: C260.2, U130.8, Y44.3
unnamed: C259.2, U130.7, Y44.1
unnamed: J87.D-, U130.6
unnamed: J87.D+, U130.5
unnamed: D88.C, U132.4
unnamed: D89.A, R90.1
unnamed: D90.A, R89.1
unnamed: C266.2, U133.8, Y45.3
unnamed: C265.2, U133.7, Y45.1
unnamed: J89.D-, U133.6
unnamed: J89.D+, U133.5
unnamed: D90.C, U135.4
unnamed: D91.A, R92.1
unnamed: D92.A, R91.1
unnamed: C272.2, U136.8, Y46.3
unnamed: C271.2, U136.7, Y46.1
unnamed: J91.D-, U136.6
unnamed: J91.D+, U136.5
unnamed: D92.C, U138.4
unnamed: D93.A, R94.1
unnamed: D94.A, R93.1
unnamed: C278.2, U139.8, Y47.3
unnamed: C277.2, U139.7, Y47.1
unnamed: J93.D-, U139.6
unnamed: J93.D+, U139.5
unnamed: D94.C, U141.4
unnamed: D95.A, R96.1
unnamed: D96.A, R95.1
unnamed: C284.2, U142.8, Y48.3
unnamed: C283.2, U142.7, Y48.1
unnamed: J95.D-, U142.6
unnamed: J95.D+, U142.5
unnamed: D96.C, U144.4
unnamed: D97.A, R98.1
unnamed: D98.A, R97.1
unnamed: C290.2, U145.8, Y49.3
unnamed: C289.2, U145.7, Y49.1
unnamed: J97.D-, U145.6
unnamed: J97.D+, U145.5
unnamed: D98.C, U147.4
unnamed: D99.A, R100.1
unnamed: D100.A, R99.1
unnamed: C296.2, U148.8, Y50.3
unnamed: C295.2, U148.7, Y50.1
unnamed: J99.D-, U148.6
unnamed: J99.D+, U148.5
unnamed: D100.C, U150.4
RXI: J2.5, U2.3, U4.1, U4.2
RXI1: J4.5, U3.3, U6.1, U6.2
RXI2: J6.5, U7.3, U9.1, U9.2
RXI3: J8.5, U10.3, U12.1, U12.2
RXI4: J10.5, U13.3, U15.1, U15.2
RXI5: J12.5, U16.3, U18.1, U18.2
RXI6: J14.5, U19.3, U21.1, U21.2
RXI7: J16.5, U22.3, U24.1, U24.2
RXI8: J18.5, U25.3, U27.1, U27.2
RXI9: J20.5, U28.3, U30.1, U30.2
RXI10: J22.5, U31.3, U33.1, U33.2
RXI11: J24.5, U34.3, U36.1, U36.2
RXI12: J26.5, U37.3, U39.1, U39.2
RXI13: J28.5, U40.3, U42.1, U42.2
RXI14: J30.5, U43.3, U45.1, U45.2
RXI15: J32.5, U46.3, U48.1, U48.2
RXI16: J34.5, U49.3, U51.1, U51.2
RXI17: J36.5, U52.3, U54.1, U54.2
RXI18: J38.5, U55.3, U57.1, U57.2
RXI19: J40.5, U58.3, U60.1, U60.2
RXI20: J42.5, U61.3, U63.1, U63.2
RXI21: J44.5, U64.3, U66.1, U66.2
RXI22: J46.5, U67.3, U69.1, U69.2
RXI23: J48.5, U70.3, U72.1, U72.2
RXI24: J50.5, U73.3, U75.1, U75.2
RXI25: J52.5, U76.3, U78.1, U78.2
RXI26: J54.5, U79.3, U81.1, U81.2
RXI27: J56.5, U82.3, U84.1, U84.2
RXI28: J58.5, U85.3, U87.1, U87.2
RXI29: J60.5, U88.3, U90.1, U90.2
RXI30: J62.5, U91.3, U93.1, U93.2
RXI31: J64.5, U94.3, U96.1, U96.2
RXI32: J66.5, U97.3, U99.1, U99.2
RXI33: J68.5, U100.3, U102.1, U102.2
RXI34: J70.5, U103.3, U105.1, U105.2
RXI35: J72.5, U106.3, U108.1, U108.2
RXI36: J74.5, U109.3, U111.1, U111.2
RXI37: J76.5, U112.3, U114.1, U114.2
RXI38: J78.5, U115.3, U117.1, U117.2
RXI39: J80.5, U118.3, U120.1, U120.2
RXI40: J82.5, U121.3, U123.1, U123.2
RXI41: J84.5, U124.3, U126.1, U126.2
RXI42: J86.5, U127.3, U129.1, U129.2
RXI43: J88.5, U130.3, U132.1, U132.2
RXI44: J90.5, U133.3, U135.1, U135.2
RXI45: J92.5, U136.3, U138.1, U138.2
RXI46: J94.5, U139.3, U141.1, U141.2
RXI47: J96.5, U142.3, U144.1, U144.2
RXI48: J98.5, U145.3, U147.1, U147.2
RXI49: J100.5, U148.3, U150.1, U150.2
SHLD: J1.SHIELD1, J1.SHIELD2, J1.SHIELD3
SHLD1: J3.SHIELD1, J3.SHIELD2, J3.SHIELD3
SHLD2: J5.SHIELD1, J5.SHIELD2, J5.SHIELD3
SHLD3: J7.SHIELD1, J7.SHIELD2, J7.SHIELD3
SHLD4: J9.SHIELD1, J9.SHIELD2, J9.SHIELD3
SHLD5: J11.SHIELD1, J11.SHIELD2, J11.SHIELD3
SHLD6: J13.SHIELD1, J13.SHIELD2, J13.SHIELD3
SHLD7: J15.SHIELD1, J15.SHIELD2, J15.SHIELD3
SHLD8: J17.SHIELD1, J17.SHIELD2, J17.SHIELD3
SHLD9: J19.SHIELD1, J19.SHIELD2, J19.SHIELD3
SHLD10: J21.SHIELD1, J21.SHIELD2, J21.SHIELD3
SHLD11: J23.SHIELD1, J23.SHIELD2, J23.SHIELD3
SHLD12: J25.SHIELD1, J25.SHIELD2, J25.SHIELD3
SHLD13: J27.SHIELD1, J27.SHIELD2, J27.SHIELD3
SHLD14: J29.SHIELD1, J29.SHIELD2, J29.SHIELD3
SHLD15: J31.SHIELD1, J31.SHIELD2, J31.SHIELD3
SHLD16: J33.SHIELD1, J33.SHIELD2, J33.SHIELD3
SHLD17: J35.SHIELD1, J35.SHIELD2, J35.SHIELD3
SHLD18: J37.SHIELD1, J37.SHIELD2, J37.SHIELD3
SHLD19: J39.SHIELD1, J39.SHIELD2, J39.SHIELD3
SHLD20: J41.SHIELD1, J41.SHIELD2, J41.SHIELD3
SHLD21: J43.SHIELD1, J43.SHIELD2, J43.SHIELD3
SHLD22: J45.SHIELD1, J45.SHIELD2, J45.SHIELD3
SHLD23: J47.SHIELD1, J47.SHIELD2, J47.SHIELD3
SHLD24: J49.SHIELD1, J49.SHIELD2, J49.SHIELD3
SHLD25: J51.SHIELD1, J51.SHIELD2, J51.SHIELD3
SHLD26: J53.SHIELD1, J53.SHIELD2, J53.SHIELD3
SHLD27: J55.SHIELD1, J55.SHIELD2, J55.SHIELD3
SHLD28: J57.SHIELD1, J57.SHIELD2, J57.SHIELD3
SHLD29: J59.SHIELD1, J59.SHIELD2, J59.SHIELD3
SHLD30: J61.SHIELD1, J61.SHIELD2, J61.SHIELD3
SHLD31: J63.SHIELD1, J63.SHIELD2, J63.SHIELD3
SHLD32: J65.SHIELD1, J65.SHIELD2, J65.SHIELD3
SHLD33: J67.SHIELD1, J67.SHIELD2, J67.SHIELD3
SHLD34: J69.SHIELD1, J69.SHIELD2, J69.SHIELD3
SHLD35: J71.SHIELD1, J71.SHIELD2, J71.SHIELD3
SHLD36: J73.SHIELD1, J73.SHIELD2, J73.SHIELD3
SHLD37: J75.SHIELD1, J75.SHIELD2, J75.SHIELD3
SHLD38: J77.SHIELD1, J77.SHIELD2, J77.SHIELD3
SHLD39: J79.SHIELD1, J79.SHIELD2, J79.SHIELD3
SHLD40: J81.SHIELD1, J81.SHIELD2, J81.SHIELD3
SHLD41: J83.SHIELD1, J83.SHIELD2, J83.SHIELD3
SHLD42: J85.SHIELD1, J85.SHIELD2, J85.SHIELD3
SHLD43: J87.SHIELD1, J87.SHIELD2, J87.SHIELD3
SHLD44: J89.SHIELD1, J89.SHIELD2, J89.SHIELD3
SHLD45: J91.SHIELD1, J91.SHIELD2, J91.SHIELD3
SHLD46: J93.SHIELD1, J93.SHIELD2, J93.SHIELD3
SHLD47: J95.SHIELD1, J95.SHIELD2, J95.SHIELD3
SHLD48: J97.SHIELD1, J97.SHIELD2, J97.SHIELD3
SHLD49: J99.SHIELD1, J99.SHIELD2, J99.SHIELD3
TXO: D1.C, J2.4, U2.2
TXO1: D3.C, J4.4, U3.2
TXO2: D5.C, J6.4, U7.2
TXO3: D7.C, J8.4, U10.2
TXO4: D9.C, J10.4, U13.2
TXO5: D11.C, J12.4, U16.2
TXO6: D13.C, J14.4, U19.2
TXO7: D15.C, J16.4, U22.2
TXO8: D17.C, J18.4, U25.2
TXO9: D19.C, J20.4, U28.2
TXO10: D21.C, J22.4, U31.2
TXO11: D23.C, J24.4, U34.2
TXO12: D25.C, J26.4, U37.2
TXO13: D27.C, J28.4, U40.2
TXO14: D29.C, J30.4, U43.2
TXO15: D31.C, J32.4, U46.2
TXO16: D33.C, J34.4, U49.2
TXO17: D35.C, J36.4, U52.2
TXO18: D37.C, J38.4, U55.2
TXO19: D39.C, J40.4, U58.2
TXO20: D41.C, J42.4, U61.2
TXO21: D43.C, J44.4, U64.2
TXO22: D45.C, J46.4, U67.2
TXO23: D47.C, J48.4, U70.2
TXO24: D49.C, J50.4, U73.2
TXO25: D51.C, J52.4, U76.2
TXO26: D53.C, J54.4, U79.2
TXO27: D55.C, J56.4, U82.2
TXO28: D57.C, J58.4, U85.2
TXO29: D59.C, J60.4, U88.2
TXO30: D61.C, J62.4, U91.2
TXO31: D63.C, J64.4, U94.2
TXO32: D65.C, J66.4, U97.2
TXO33: D67.C, J68.4, U100.2
TXO34: D69.C, J70.4, U103.2
TXO35: D71.C, J72.4, U106.2
TXO36: D73.C, J74.4, U109.2
TXO37: D75.C, J76.4, U112.2
TXO38: D77.C, J78.4, U115.2
TXO39: D79.C, J80.4, U118.2
TXO40: D81.C, J82.4, U121.2
TXO41: D83.C, J84.4, U124.2
TXO42: D85.C, J86.4, U127.2
TXO43: D87.C, J88.4, U130.2
TXO44: D89.C, J90.4, U133.2
TXO45: D91.C, J92.4, U136.2
TXO46: D93.C, J94.4, U139.2
TXO47: D95.C, J96.4, U142.2
TXO48: D97.C, J98.4, U145.2
TXO49: D99.C, J100.4, U148.2
V1: C11.1, U3.4
V2: C17.1, U7.4
V3: C6.1, U2.4
V4: C23.1, U10.4
V5: C29.1, U13.4
V6: C35.1, U16.4
V7: C41.1, U19.4
V8: C47.1, U22.4
V9: C53.1, U25.4
V10: C59.1, U28.4
V11: C65.1, U31.4
V12: C71.1, U34.4
V13: C77.1, U37.4
V14: C83.1, U40.4
V15: C89.1, U43.4
V16: C95.1, U46.4
V17: C101.1, U49.4
V18: C107.1, U52.4
V19: C113.1, U55.4
V20: C119.1, U58.4
V21: C125.1, U61.4
V22: C131.1, U64.4
V23: C137.1, U67.4
V24: C143.1, U70.4
V25: C149.1, U73.4
V26: C155.1, U76.4
V27: C161.1, U79.4
V28: C167.1, U82.4
V29: C173.1, U85.4
V30: C179.1, U88.4
V31: C185.1, U91.4
V32: C191.1, U94.4
V33: C197.1, U97.4
V34: C203.1, U100.4
V35: C209.1, U103.4
V36: C215.1, U106.4
V37: C221.1, U109.4
V38: C227.1, U112.4
V39: C233.1, U115.4
V40: C239.1, U118.4
V41: C245.1, U121.4
V42: C251.1, U124.4
V43: C257.1, U127.4
V44: C263.1, U130.4
V45: C269.1, U133.4
V46: C275.1, U136.4
V47: C281.1, U139.4
V48: C287.1, U142.4
V49: C293.1, U145.4
V50: C299.1, U148.4
VCC: C3.1, J2.3, JP1.2, R2.2, R3.2, U2.16, U4.5
VCC1: C12.1, J4.3, JP10.2, R1.2, R4.2, U3.16, U6.5
VCC2: C18.1, J6.3, JP15.2, R5.2, R6.2, U7.16, U9.5
VCC3: C24.1, J8.3, JP20.2, R7.2, R8.2, U10.16, U12.5
VCC4: C30.1, J10.3, JP25.2, R9.2, R10.2, U13.16, U15.5
VCC5: C36.1, J12.3, JP30.2, R11.2, R12.2, U16.16, U18.5
VCC6: C42.1, J14.3, JP35.2, R13.2, R14.2, U19.16, U21.5
VCC7: C48.1, J16.3, JP40.2, R15.2, R16.2, U22.16, U24.5
VCC8: C54.1, J18.3, JP45.2, R17.2, R18.2, U25.16, U27.5
VCC9: C60.1, J20.3, JP50.2, R19.2, R20.2, U28.16, U30.5
VCC10: C66.1, J22.3, JP55.2, R21.2, R22.2, U31.16, U33.5
VCC11: C72.1, J24.3, JP60.2, R23.2, R24.2, U34.16, U36.5
VCC12: C78.1, J26.3, JP65.2, R25.2, R26.2, U37.16, U39.5
VCC13: C84.1, J28.3, JP70.2, R27.2, R28.2, U40.16, U42.5
VCC14: C90.1, J30.3, JP75.2, R29.2, R30.2, U43.16, U45.5
VCC15: C96.1, J32.3, JP80.2, R31.2, R32.2, U46.16, U48.5
VCC16: C102.1, J34.3, JP85.2, R33.2, R34.2, U49.16, U51.5
VCC17: C108.1, J36.3, JP90.2, R35.2, R36.2, U52.16, U54.5
VCC18: C114.1, J38.3, JP95.2, R37.2, R38.2, U55.16, U57.5
VCC19: C120.1, J40.3, JP100.2, R39.2, R40.2, U58.16, U60.5
VCC20: C126.1, J42.3, JP105.2, R41.2, R42.2, U61.16, U63.5
VCC21: C132.1, J44.3, JP110.2, R43.2, R44.2, U64.16, U66.5
VCC22: C138.1, J46.3, JP115.2, R45.2, R46.2, U67.16, U69.5
VCC23: C144.1, J48.3, JP120.2, R47.2, R48.2, U70.16, U72.5
VCC24: C150.1, J50.3, JP125.2, R49.2, R50.2, U73.16, U75.5
VCC25: C156.1, J52.3, JP130.2, R51.2, R52.2, U76.16, U78.5
VCC26: C162.1, J54.3, JP135.2, R53.2, R54.2, U79.16, U81.5
VCC27: C168.1, J56.3, JP140.2, R55.2, R56.2, U82.16, U84.5
VCC28: C174.1, J58.3, JP145.2, R57.2, R58.2, U85.16, U87.5
VCC29: C180.1, J60.3, JP150.2, R59.2, R60.2, U88.16, U90.5
VCC30: C186.1, J62.3, JP155.2, R61.2, R62.2, U91.16, U93.5
VCC31: C192.1, J64.3, JP160.2, R63.2, R64.2, U94.16, U96.5
VCC32: C198.1, J66.3, JP165.2, R65.2, R66.2, U97.16, U99.5
VCC33: C204.1, J68.3, JP170.2, R67.2, R68.2, U100.16, U102.5
VCC34: C210.1, J70.3, JP175.2, R69.2, R70.2, U103.16, U105.5
VCC35: C216.1, J72.3, JP180.2, R71.2, R72.2, U106.16, U108.5
VCC36: C222.1, J74.3, JP185.2, R73.2, R74.2, U109.16, U111.5
VCC37: C228.1, J76.3, JP190.2, R75.2, R76.2, U112.16, U114.5
VCC38: C234.1, J78.3, JP195.2, R77.2, R78.2, U115.16, U117.5
VCC39: C240.1, J80.3, JP200.2, R79.2, R80.2, U118.16, U120.5
VCC40: C246.1, J82.3, JP205.2, R81.2, R82.2, U121.16, U123.5
VCC41: C252.1, J84.3, JP210.2, R83.2, R84.2, U124.16, U126.5
VCC42: C258.1, J86.3, JP215.2, R85.2, R86.2, U127.16, U129.5
VCC43: C264.1, J88.3, JP220.2, R87.2, R88.2, U130.16, U132.5
VCC44: C270.1, J90.3, JP225.2, R89.2, R90.2, U133.16, U135.5
VCC45: C276.1, J92.3, JP230.2, R91.2, R92.2, U136.16, U138.5
VCC46: C282.1, J94.3, JP235.2, R93.2, R94.2, U139.16, U141.5
VCC47: C288.1, J96.3, JP240.2, R95.2, R96.2, U142.16, U144.5
VCC48: C294.1, J98.3, JP245.2, R97.2, R98.2, U145.16, U147.5
VCC49: C300.1, J100.3, JP250.2, R99.2, R100.2, U148.16, U150.5

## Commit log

2016-09-20 :lollipop: Added .gitattributes & .gitignore files
2016-09-20 Initial PCB layout
2016-09-20 Added TP to 3.3V. Passes checklist.
2016-09-22 Many hardware changes from review.
    Moved 0.1uF closer to IC, changed to VCC net. Added via anchors to
    microB. Silk bumps. PCB width increase.
2016-09-22 Repo name change and readme update
2016-09-23 Fixing issues #1, #2, #3, #4
2016-10-25 Changing resistor on Greeg LED to 330
2016-10-25 Fixing DRC error
2016-11-01 Adding buffer to RX line.
2016-11-02 Adding PROD_ID to AND gate
2016-11-02 Add arrow to VCC net
2016-11-08 panel
2017-02-09 updating product description and documentation links in readme, adding license file
